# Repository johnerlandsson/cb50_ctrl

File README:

Control system for a rebuilt Camurri CB50 brewkettle.

Author: John Erlandsson
License: GPLV3

cb50_ctrl - C++ application for controling I/O and serving HMI pages
www - Web application implemented using angularjs and bootstrap
kmod - Drivers for raspberrypi gpio

Build
Recommended to build in separate folder
mkdir build
cd build
cmake ..
make

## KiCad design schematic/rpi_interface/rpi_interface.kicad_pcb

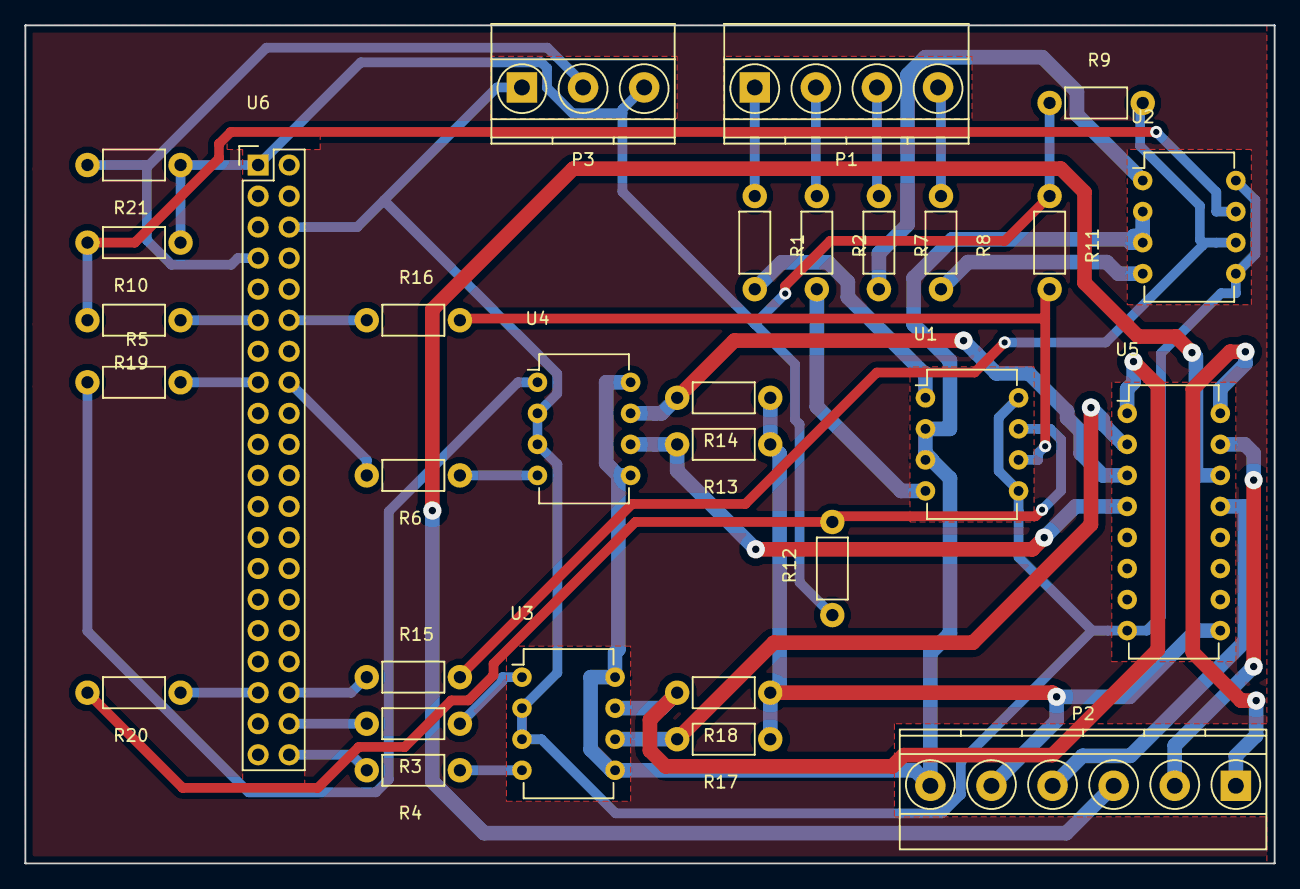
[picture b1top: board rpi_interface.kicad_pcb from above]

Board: 2 copper layers, 102.2 x 68.6 mm, 30 parts (0 on the bottom side), 37 nets.

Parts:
P1: CONN_01X04; TerminalBlock_Pheonix_MKDS1.5-4pol
P2: CONN_01X06; TerminalBlock_Pheonix_MKDS1.5-6pol
P3: CONN_01X03; TerminalBlock_Pheonix_MKDS1.5-3pol
R1, R2, R3, R4, R5, R6, R7, R8: R; Resistor_Horizontal_RM7mm
R9, R10, R11, R12: 10k; Resistor_Horizontal_RM7mm
R13, R14, R17, R18: 50k; Resistor_Horizontal_RM7mm
R15, R16, R19, R20: 1k; Resistor_Horizontal_RM7mm
R21: 4.7k; Resistor_Horizontal_RM7mm
U1, U2, U3, U4: MCT6; DIP-8_W7.62mm
U5: ULN2003; DIP-16_W7.62mm
U6: Raspberry_Pi_2_3; Pin_Header_Straight_2x20

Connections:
+3V3: P3.3, R9.1, R10.1, R11.1, R12.1, R21.1, U6.1
+24V: P2.5, R13.1, R14.1, R17.1, R18.1, U5.9
/inpMixerButton: P1.2, R2.1
/inpPumpButton: P1.3, R7.1
/inpSpare01: P1.4, R8.1
/inpStartButton: P1.1, R1.1
/outpMixer: R4.2, U6.40
/outpPump: R5.2, U6.15
/outpRadiator: R3.2, U6.38
/outpSpare01: R6.2, U6.16
GND: P3.1, U1.5, U1.8, U2.5, U2.8, U3.2, U3.3, U4.2, U4.3, U5.8, U6.6
GNDA: P2.6, U1.2, U1.3, U2.2, U2.3, U3.5, U3.8, U4.5, U4.8
unnamed: P2.1, U5.16
unnamed: P2.2, U5.15
unnamed: P2.3, U5.14
unnamed: P2.4, U5.13
unnamed: P3.2, R21.2, U6.7
unnamed: R1.2, U1.1
unnamed: R2.2, U1.4
unnamed: R3.1, U3.1
unnamed: R4.1, U3.4
unnamed: R5.1, U4.1
unnamed: R6.1, U4.4
unnamed: R7.2, U2.1
unnamed: R8.2, U2.4
unnamed: R10.2, R19.2, U2.7
unnamed: R11.2, R16.2, U1.6
unnamed: R12.2, R20.2, U1.7
unnamed: R13.2, U4.6, U5.4
unnamed: R14.2, U4.7, U5.3
unnamed: R15.1, U6.36
unnamed: R9.2, R15.2, U2.6
unnamed: R16.1, U6.12
unnamed: R17.2, U3.6, U5.2
unnamed: R18.2, U3.7, U5.1
unnamed: R19.1, U6.11
unnamed: R20.1, U6.35

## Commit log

2017-03-16 to and from json methods implemented in Parameters
2017-03-17 Added from wvalue method
2017-03-17 Started working on web stuff
2017-03-17 Added static routing
2017-03-20 Added general stylesheet
2017-03-20 Added fontawesome
2017-03-21 Working on trend
2017-03-22 Struggling with angularjs
2017-03-22 Refined routing
2017-03-22 Started working on trend request
2017-03-23 Trend sort of working
2017-03-23 Changed icon position for pages and formatted date string as ISO
2017-03-23 get parameters working
2017-03-23 Added notifications
2017-03-24 Implemented put parameters on server
2017-03-24 Restructured project dir
2017-03-24 Adjusted .gitignore
2017-03-24 added kernel module
2017-03-24 Fixed typeos
2017-03-24 License stuff
2017-03-24 Started working on log
2017-03-27 Added database class. Replaced log and parameter classes with this one
2017-03-27 Log works
2017-03-30 Styling pages
2017-03-30 Added ProcessValue
2017-03-30 Added button group to recipe
2017-03-31 Started drawing schematic
2017-03-31 Removed json file
2017-03-31 Read pd done
2017-03-31 Added notification stylesheet to index and log
2017-04-02 Wrapped process data in class
2017-04-02 Working on sending pd
2017-04-03 Toolbar working
2017-04-03 Tuned button functionality
2017-04-03 Added license info to new classes
2017-04-03 Fixed compile warning c++14
2017-04-03 Fixed border issue with buttons
2017-04-05 Started drawing interface board
2017-04-05 More schematic work
2017-04-05 In phase with workstation
2017-04-06 Started working on recipe
2017-04-07 Worked out how to iterate wvalue array
2017-04-10 working on recipe class
2017-04-11 Loading recipes from database now working
2017-04-11 Added license info to Recipe sources
2017-04-12 Tinkering with recipe browser
2017-04-12 Added lists to browser
2017-04-13 Syncing recipes now work
2017-04-13 Forgot web changes
2017-04-15 Fixed quotation bug in get recipe
2017-04-15 Working on recipe browser
2017-04-18 Added functionality to insert new recipe
2017-04-18 More work on selection model for recipe browser
2017-04-18 Added functionality to append entry to recipe
2017-04-18 Added sound file
2017-04-21 Added recipe viewer
2017-04-21 Thermometer working
